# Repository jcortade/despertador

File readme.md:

# Alarm clock based on ESP32

This is an alarm clock based on ESP32 programmed in micropython. Its main features are:

- Four digits seven segments display. Oldie but goodie.
- Three push buttons for alarm time selection.
- LM386 audio power amplifier with a 1W speaker. It plays Tetris tune.
- LDR used to power off the display in the dark.
- PIR detector to see time in the dark and turn off the alarm.
- "Dimmable" LED using PWM ouput.
- It connects via wifi to an NTP server and synchronize automatically. It also even calculates summer/winter time!

Prototyping phase:

Preparing PCB for solder paste application:

PCB with components soldered:

Final result:

PCB was designed with kiCAD. 

3D printed alarm clock body was designed with FreeCAD. 

Inspired by this project: https://github.com/thedalles77/Raspberry-Pi-Pico-LED-Alarm-Clock

Audio player idea from here: https://circuitdigest.com/microcontroller-projects/esp32-based-audio-player

Tetris tune acknowledgements: https://assets.codeclubau.org/assets/tetris-theme.pdf

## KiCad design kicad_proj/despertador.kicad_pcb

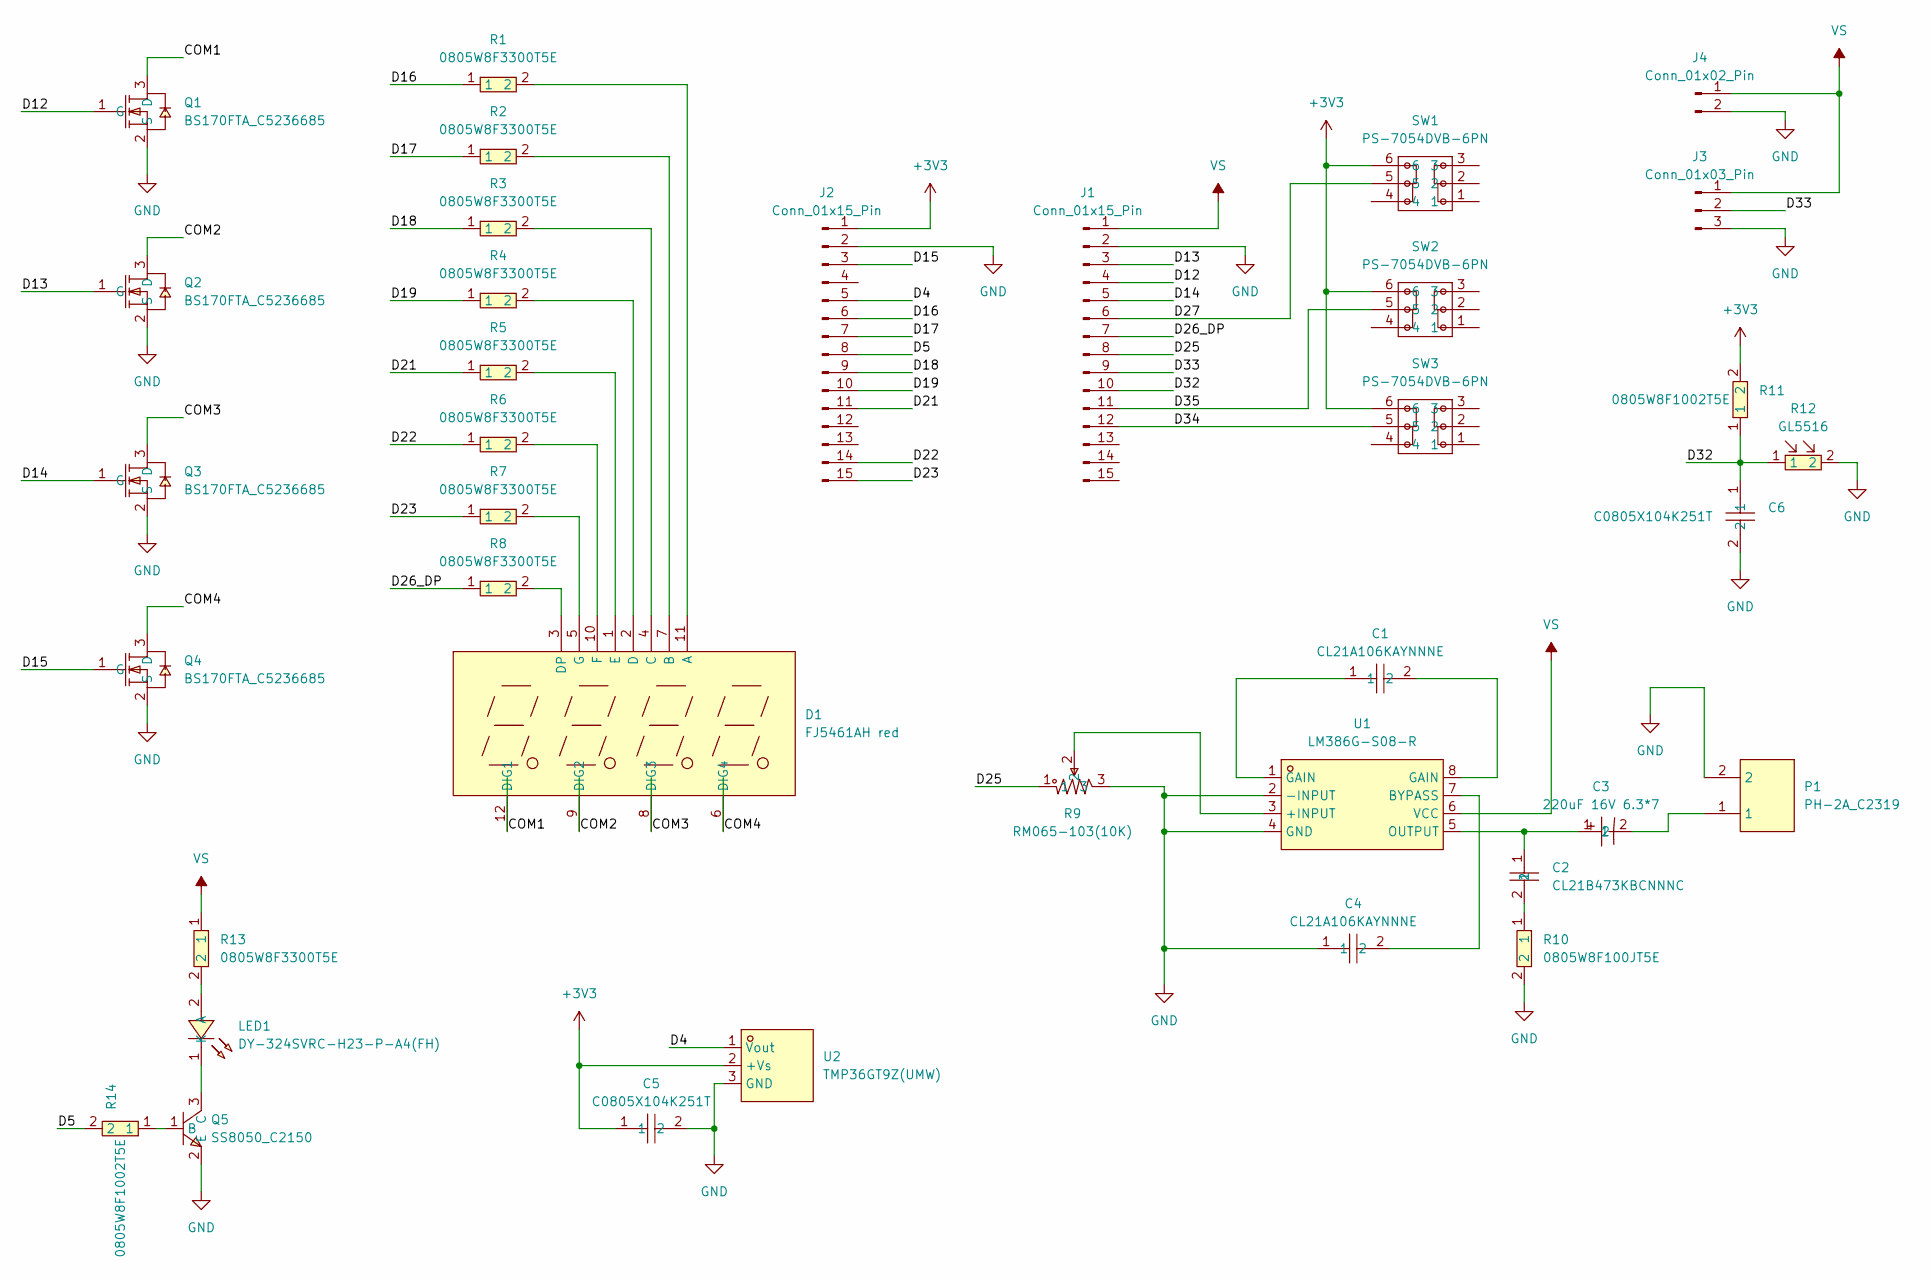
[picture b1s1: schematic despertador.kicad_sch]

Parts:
C1, C4: CL21A106KAYNNNE; C0805; LCSC Part C15850
C2: CL21B473KBCNNNC; C0805; LCSC Part C53134
C3: 220uF 16V 6.3*7; CAP-TH_BD6.3-P2.50-D1.0-FD; LCSC Part C43340
C5, C6: C0805X104K251T; C0805; LCSC Part C5451689
D1: FJ5461AH red; LED-SEG-TH_FJ5461AH; LCSC Part C54396
J1, J2: Conn_01x15_Pin; PinHeader_1x15_P2.54mm_Vertical
J3: Conn_01x03_Pin; PinHeader_1x03_P2.54mm_Vertical
J4: Conn_01x02_Pin; PinHeader_2x01_P2.54mm_Vertical
LED1: DY-324SVRC-H23-P-A4(FH); LED-TH_BD5.8-P2.54-RD; LCSC Part C7470729
P1: PH-2A_C2319; CONN-TH_2P-P2.00_PH-2A_C2319; LCSC Part C2319
Q1, Q2, Q3, Q4: BS170FTA_C5236685; SOT-23-3_L2.9-W1.3-P1.90-LS2.4-BR; LCSC Part C5236685
Q5: SS8050_C2150; SOT-23-3_L2.9-W1.3-P1.90-LS2.4-BR; LCSC Part C2150
R1, R2, R3, R4, R5, R6, R7, R8, R13: 0805W8F3300T5E; R0805; LCSC Part C17630
R9: RM065-103(10K); RES-ADJ-SMD_RM065-V1; LCSC Part C5205021
R10: 0805W8F100JT5E; R0805_NEW; LCSC Part C17415
R11, R14: 0805W8F1002T5E; R0805; LCSC Part C17414
R12: GL5516; RES-TH_L5.1-W4.3-P3.40-D0.5; LCSC Part C125626
SW1, SW2, SW3: PS-7054DVB-6PN; SW-TH_6P-L7.0-W7.0-P2.00; LCSC Part C22363820
U1: LM386G-S08-R; SOP-8_L4.9-W3.9-P1.27-LS6.0-BL; LCSC Part C85119
U2: TMP36GT9Z(UMW); TO-92-3_L4.8-W3.7-P2.54-L; LCSC Part C5692995

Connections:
+3V3: C5.1, J2.1, R11.2, SW1.6, SW2.6, SW3.6, U2.2 (+Vs)
/COM1: D1.12 (DIG1), Q1.3 (D)
/COM2: D1.9 (DIG2), Q2.3 (D)
/COM3: D1.8 (DIG3), Q3.3 (D)
/COM4: D1.6 (DIG4), Q4.3 (D)
/D4: J2.5, U2.1 (Vout)
/D5: J2.8, R14.2
/D12: J1.4, Q1.1 (G)
/D13: J1.3, Q2.1 (G)
/D14: J1.5, Q3.1 (G)
/D15: J2.3, Q4.1 (G)
/D16: J2.6, R1.1
/D17: J2.7, R2.1
/D18: J2.9, R3.1
/D19: J2.10, R4.1
/D21: J2.11, R5.1
/D22: J2.14, R6.1
/D23: J2.15, R7.1
/D25: J1.8, R9.1
/D26_DP: J1.7, R8.1
/D27: J1.6, SW1.5
/D32: C6.1, J1.10, R11.1, R12.1
/D33: J1.9, J3.2
/D34: J1.12, SW3.5
/D35: J1.11, SW2.5
GND: C4.1, C5.2, C6.2, J1.2, J2.2, J3.3, J4.2, P1.2, Q1.2 (S), Q2.2 (S), Q3.2 (S), Q4.2 (S), Q5.2 (E), R9.3, R10.2, R12.2, U1.2 (-INPUT), U1.4 (GND), U2.3 (GND)
unnamed: C1.1, U1.1 (GAIN)
unnamed: C1.2, U1.8 (GAIN)
unnamed: C2.2, R10.1
unnamed: C3.2, P1.1
unnamed: D1.11 (A), R1.2
unnamed: D1.7 (B), R2.2
unnamed: D1.4 (C), R3.2
unnamed: D1.2 (D), R4.2
unnamed: D1.3 (DP), R8.2
unnamed: D1.1 (E), R5.2
unnamed: D1.10 (F), R6.2
unnamed: D1.5 (G), R7.2
unnamed: LED1.2 (A), R13.2
unnamed: LED1.1 (K), Q5.3 (C)
unnamed: Q5.1 (B), R14.1
unnamed: R9.2, U1.3 (+INPUT)
unnamed: C4.2, U1.7 (BYPASS)
unnamed: C2.1, C3.1, U1.5 (OUTPUT)
VS: J1.1, J3.1, J4.1, R13.1, U1.6 (VCC)

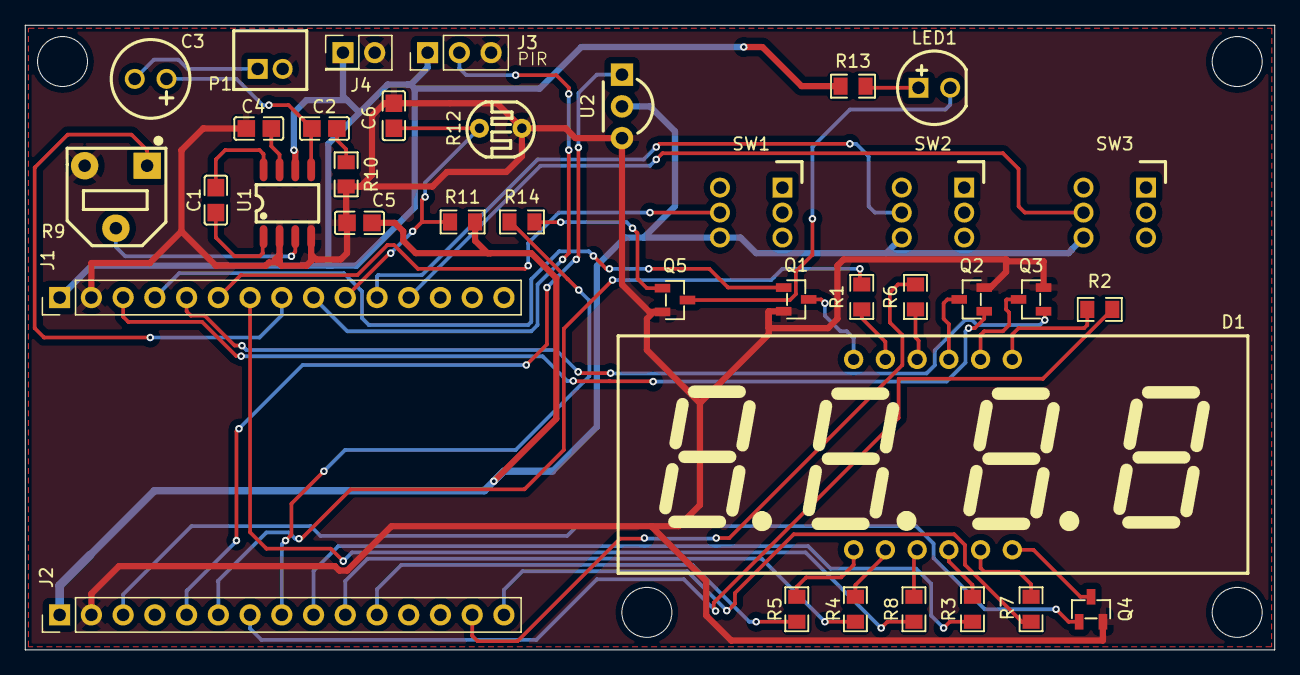
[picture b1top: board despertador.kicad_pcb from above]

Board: 2 copper layers, 100.0 x 50.0 mm, 37 parts (0 on the bottom side), 45 nets.

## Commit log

2025-07-06 wify secrets file added before ignoring it
2025-07-06 ignore updated
2025-07-06 ignore including wifi.py
2025-07-06 Added wifi.py manually via upload
2025-07-06 readme file added
2025-07-06 freeCAD project added
2025-07-06 BOM.txt deleted
2025-07-06 Deleted some files
2025-07-06 readme update
2025-07-06 Pictures added
2025-07-06 gitignore updated
2025-07-08 images and schematics added
2025-07-09 first image included in readme
2025-07-09 final result picture added
2025-07-09 Rest of images added to readme.md
2025-07-09 typos in readme...
2025-07-09 more typos in readme...
